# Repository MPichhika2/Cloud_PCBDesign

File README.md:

# Stary_PCB 
A star-shaped PCB that has a face that changes when a button is clicked. It is an AI assistant!
Purpose: The Stary PCB can take photos and talk back as an assistant when asked a question, and I might even be able to add more cool stuff once I get to connect it to the wifi. 
I wanted to make a Stary in order for it to function as a pocket assistant! 

First, I made a Schematic Design: 
I added a microcontroller (with a camera), a push button, a screen, an amplifier, and a speaker.
Then, after I wired all the parts, I transferred the design into the PCB editor. This is where I first cut out a star shape and made it with rounded edges. Then I carefully placed the schematic design by placing the screen in the middle, the camera in the upper left corner, the amplifier on the back, and the button on the right wing of the star. 

Finally I waas able to place all the parts so I can view them in the 3d view to fininalize the stary. I also added a png of a shimmer and painted some "connection" (js for it to look cool)!!

This is my final Stary design! 

### 📋 Bill of Materials (BOM)

| Reference | Qty | Value | Description |
| :--- | :---: | :--- | :--- |
| J1 | 1 | LiPo 3.7V | Battery Connector |
| J2 | 1 | LCD GC9A01 2.1IN | Round LCD Display |
| J3 | 1 | MAX98357A AUDIO | I2S Audio Amplifier |
| SW1 | 1 | SW Push | Momentary Push Button |
| U1 | 1 | XIAO-ESP32-S3-SMD | Microcontroller Board |

Battery: https://www.amazon.com/JLJLUP-Rechargeable-Integrated-Protection-Development/dp/B0FH9XHXRT/ref=sr_1_1_sspa?crid=1ZFPTSMA4R4VS&dib=eyJ2IjoiMSJ9.li4cggKoqEX1SCSDpXCjx5rcFOkZCffsMpN0MZvvsb-3ts514JaD77b9Zi0EoE2yvqWQQho6XYXZFpXVU01_6DGqK17vN5Z8FfuaJuQFyrumgg5MBa_YGPVEs4JH-amadvfSivi-WXWeFsumB_FD1lDSzuhinzHSJvADKcDifkW4G4adNW5mFZstXtEkIi1csCe7JqPzCbmqA16msmUSZQWdUL0mZaU-c17hyT1By5HbN10kOAZ3ndsB4pG1EU99eW3xAJllsy_c1jy_87fAJLbL3LeosiFYIYiWEbcxx-s.wyrMGXUMYZBJfQJD3PuQXGeb1in74XmtxEOdm40uDCM&dib_tag=se&keywords=lipo+battery&qid=1792773489&sprefix=lipo+battery%2Caps%2C141&sr=8-1-spons&sp_csd=d2lkZ2V0TmFtZT1zcF9hdGY&psc=1

 SCREEN: https://www.seeedstudio.com/XIAO-ESP32S3-Sense-p-5639.html

AMPLIFIER:https://www.adafruit.com/product/3006?srsltid=AU7gw4XkQBUtkr-MiJQN6yo5ufW_RndERFHiWExqMsFZ_fTOXYAt0ue0

BUTTON:(I ONLY NEEED ONE PIECE BUT NO ONE SELLS THAT. IS THERE AN ANOTHER WAY?) https://www.amazon.com/DAOKI-Miniature-Momentary-Tactile-Quality/dp/B01CGMP9GY/ref=sr_1_6?dib=eyJ2IjoiMSJ9.0H9GGs7qKjJ-EE5XDHapeq6keJD7doZZEm6qtEyq8T7-KaPERURoCLBFP1qOYl6YLds8TJOgMgvnXL3f1NBFE67etRNuZ9ImayEXy_1lNtqVa3t7NKQq6WhjyP7mmnWYqX3rdJgLken45dYqB4j0SRmClKEQnKvHoAArC_6PD0Mdp0Vdl72WsIPQcEg8eEw557fQPyhu0oF4hBfRM7IZeCpzchp5PWkb25Zsunbi-rU.QXzTg7w_MsQd-DoV5N1WCv5esSvixRuEVVS-i6S7Ask&dib_tag=se&keywords=tactile%2Bpush%2Bbutton%2Bswitch&qid=1791770041&sr=8-6&th=1

MICROCONTROLLER: https://www.seeedstudio.com/XIAO-ESP32S3-Sense-p-5639.html

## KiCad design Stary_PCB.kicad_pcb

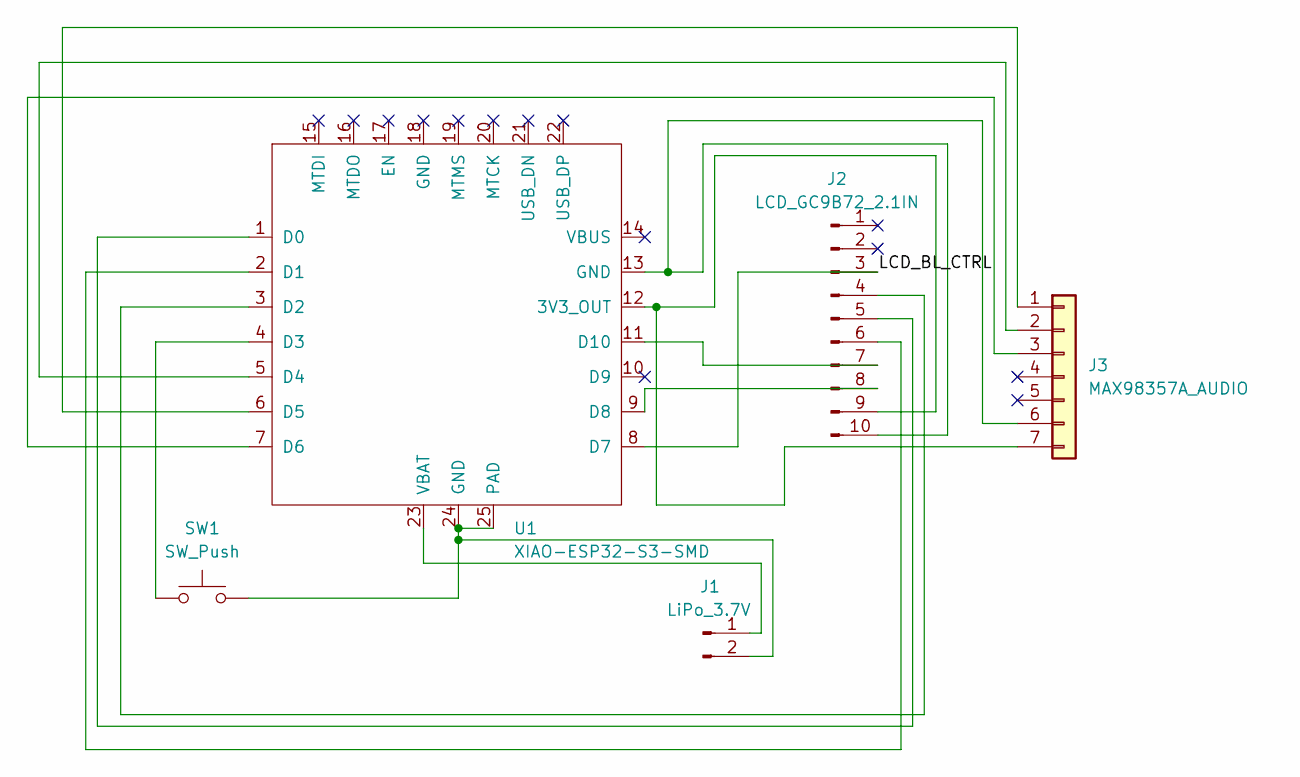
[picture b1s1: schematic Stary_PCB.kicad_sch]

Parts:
J1: LiPo_3.7V; JST_PH_S2B-PH-SM4-TB_1x02-1MP_P2.00mm_Horizontal
J2: LCD_GC9B72_2.1IN; PinSocket_1x10_P2.54mm_Vertical
J3: MAX98357A_AUDIO; Adafruit_MAX98357A_Breakout
SW1: SW_Push; SW_SPST_TL3305A
U1: XIAO-ESP32-S3-SMD

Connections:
/LCD_BL_CTRL: J2.3, U1.8 (D7)
unnamed: J1.1, U1.23 (VBAT)
unnamed: J1.2, SW1.2, U1.24 (GND), U1.25 (PAD)
unnamed: J2.4, U1.3 (D2)
unnamed: J2.5, U1.1 (D0)
unnamed: J2.6, U1.2 (D1)
unnamed: J2.7, U1.11 (D10)
unnamed: J2.8, U1.9 (D8)
unnamed: J2.9, J3.7, U1.12 (3V3_OUT)
unnamed: J2.10, J3.6, U1.13 (GND)
unnamed: J3.1, U1.6 (D5)
unnamed: J3.2, U1.5 (D4)
unnamed: J3.3, U1.7 (D6)
unnamed: SW1.1, U1.4 (D3)

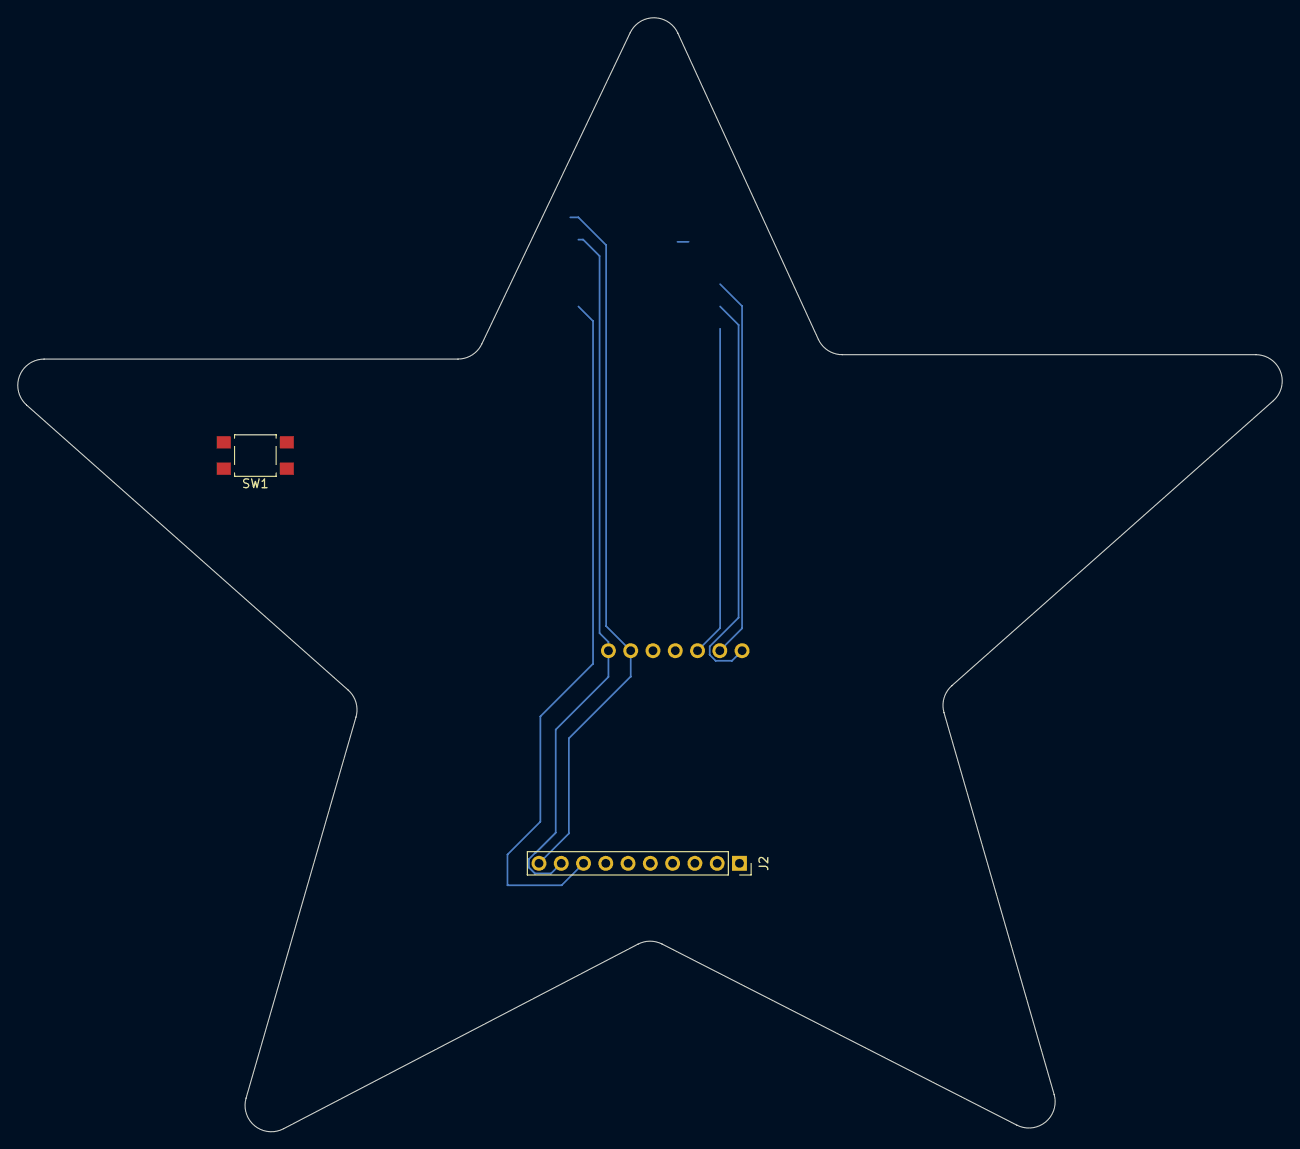
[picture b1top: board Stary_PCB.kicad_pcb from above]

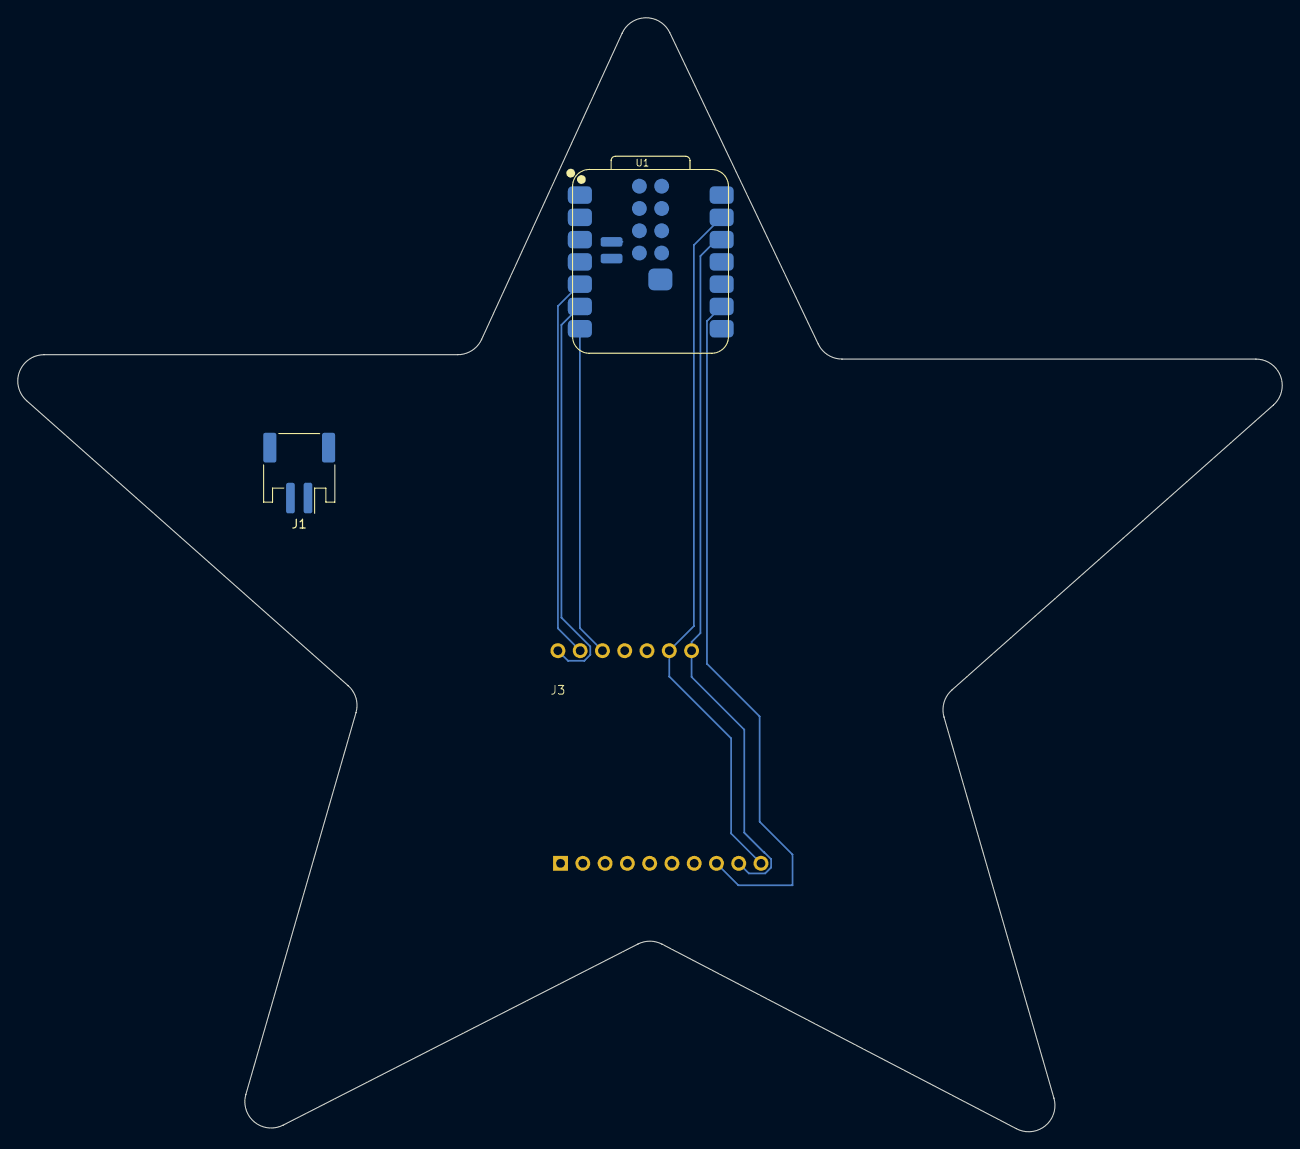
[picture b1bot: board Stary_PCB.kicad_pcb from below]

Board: 2 copper layers, 144.2 x 127.0 mm, 5 parts (3 on the bottom side), 14 nets.

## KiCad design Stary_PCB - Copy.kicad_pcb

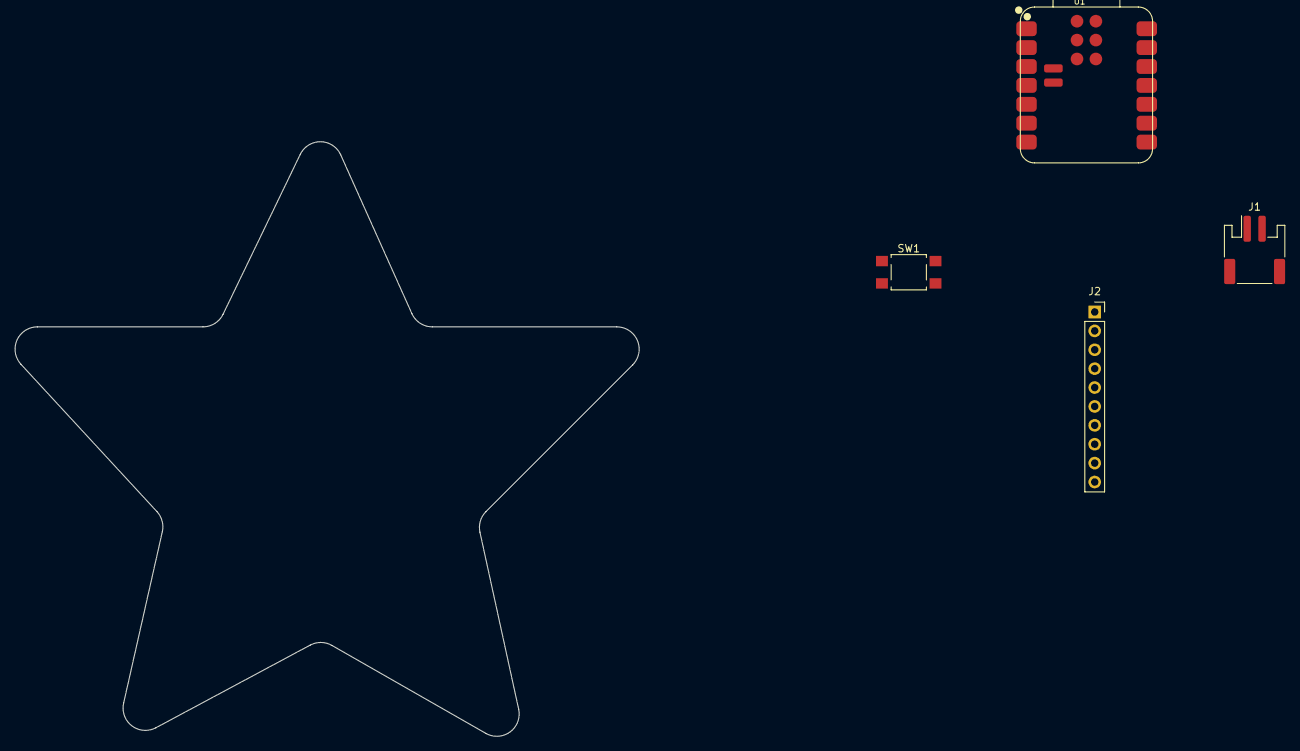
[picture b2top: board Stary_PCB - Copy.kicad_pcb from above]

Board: 2 copper layers, 83.9 x 79.9 mm, 4 parts (0 on the bottom side), 11 nets, no tracks yet.

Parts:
J1: LiPo_3.7V; JST_PH_S2B-PH-SM4-TB_1x02-1MP_P2.00mm_Horizontal
J2: LCD_GC9B72_2.1IN; PinSocket_1x10_P2.54mm_Vertical
SW1: SW_Push; SW_SPST_TL3305A
U1: XIAO-ESP32-C3-SMD

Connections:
/LCD_BL_CTRL: J2.3, U1.6 (D5)
unnamed: J1.1, U1.21 (VBAT)
unnamed: J1.2, SW1.2, U1.22 (GND)
unnamed: J2.4, U1.2 (D1)
unnamed: J2.5, U1.3 (D2)
unnamed: J2.6, U1.4 (D3)
unnamed: J2.7, U1.11 (D10)
unnamed: J2.8, U1.9 (D8)
unnamed: J2.9, U1.12 (3V3_OUT)
unnamed: J2.10, U1.13 (GND)
unnamed: SW1.1, U1.5 (D4)
